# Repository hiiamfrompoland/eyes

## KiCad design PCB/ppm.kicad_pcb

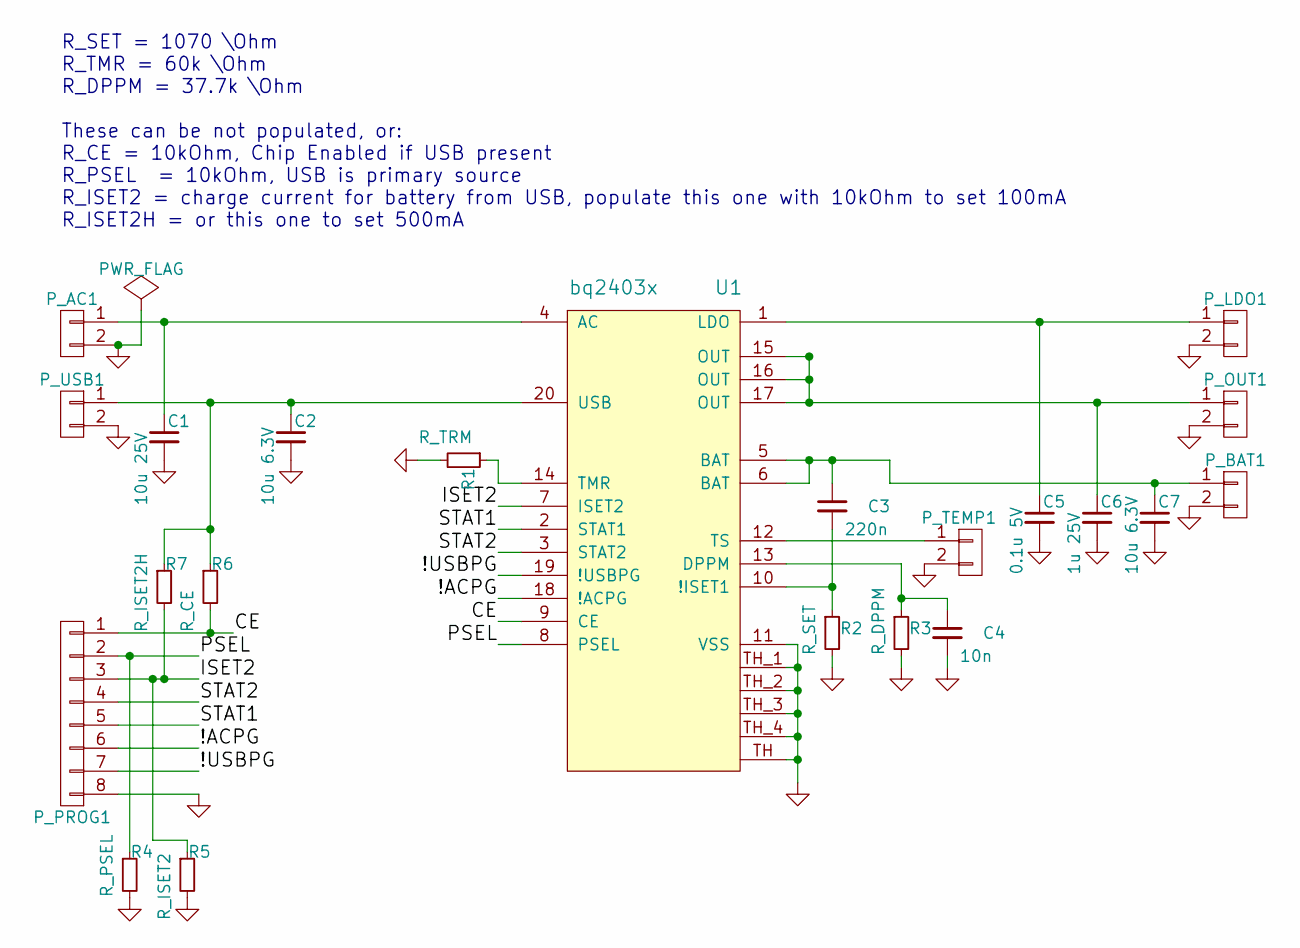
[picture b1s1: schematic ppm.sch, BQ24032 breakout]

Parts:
C1: 10u 25V; C_0603
C2, C7: 10u 6.3V; C_0603
C3: 220n; C_0603
C4: 10n; C_0603
C5: 0.1u 5V; C_0603
C6: 1u 25V; C_0603
P_AC1: CONN_01X02; PINHEAD2_1.27
P_BAT1: CONN_01X02; PINHEAD2_1.27
P_LDO1: CONN_01X02; PINHEAD2_1.27
P_OUT1: CONN_01X02; PINHEAD2_1.27
P_PROG1: CONN_01X08; PINHEAD8_1.27
P_TEMP1: CONN_01X02; PINHEAD2_1.27
P_USB1: CONN_01X02; PINHEAD2_1.27
R1: R_TRM; R_0603
R2: R_SET; R_0603
R3: R_DPPM; R_0603
R4: R_PSEL; R_0603
R5: R_ISET2; R_0603
R6: R_CE; R_0603
R7: R_ISET2H; R_0603
U1: bq2403x; PVQFN-N20

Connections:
/!ACPG: P_PROG1.6, U1.18 (!ACPG)
/!USBPG: P_PROG1.7, U1.19 (!USBPG)
/CE: P_PROG1.1, R6.2, U1.9 (CE)
/ISET2: P_PROG1.3, R5.1, R7.2, U1.7 (ISET2)
/PSEL: P_PROG1.2, R4.1, U1.8 (PSEL)
/STAT1: P_PROG1.5, U1.2 (STAT1)
/STAT2: P_PROG1.4, U1.3 (STAT2)
GND: C1.2, C2.2, C4.2, C5.2, C6.2, C7.2, P_AC1.2, P_BAT1.2, P_LDO1.2, P_OUT1.2, P_PROG1.8, P_TEMP1.2, P_USB1.2, R1.2, R2.2, R3.2, R4.2, R5.2, U1.11 (VSS), U1.TH, U1.TH_1, U1.TH_2, U1.TH_3, U1.TH_4
unnamed: C1.1, P_AC1.1, U1.4 (AC)
unnamed: C2.1, P_USB1.1, R6.1, R7.1, U1.20 (USB)
unnamed: C3.1, C7.1, P_BAT1.1, U1.5 (BAT), U1.6 (BAT)
unnamed: C3.2, R2.1, U1.10 (!ISET1)
unnamed: C4.1, R3.1, U1.13 (DPPM)
unnamed: C5.1, P_LDO1.1, U1.1 (LDO)
unnamed: C6.1, P_OUT1.1, U1.15 (OUT), U1.16 (OUT), U1.17 (OUT)
unnamed: P_TEMP1.1, U1.12 (TS)
unnamed: R1.1, U1.14 (TMR)

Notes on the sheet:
R_SET = 1070 \Ohm R_TMR = 60k \Ohm R_DPPM = 37.7k \Ohm These can be not populated, or: R_CE = 10kOhm, Chip Enabled if USB present R_PSEL = 10kOhm, USB is primary source R_ISET2 = charge current for battery from USB, populate this one with 10kOhm to set 100mA R_ISET2H = or this one to set 500mA

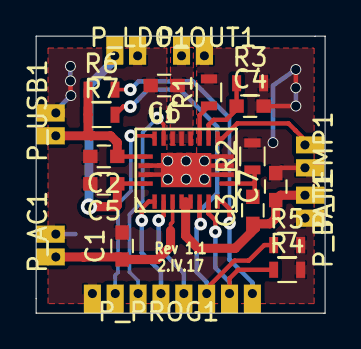
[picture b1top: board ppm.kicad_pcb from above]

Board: 2 copper layers, 16.1 x 15.4 mm, 22 parts (0 on the bottom side), 17 nets.

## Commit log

2017-04-11 Created repo
2017-04-11 Prepared for github
2017-04-21 PCB fix, Docs updated, more quaternions
2017-04-28 Cleaning up code a bit
2017-04-28 Added few files
2017-04-28 Added button functionality to code, but no button in place :(
2017-04-30 Added delete files function, docs update
2017-04-30 Added 3d model for printing
2017-04-30 TODOs update
